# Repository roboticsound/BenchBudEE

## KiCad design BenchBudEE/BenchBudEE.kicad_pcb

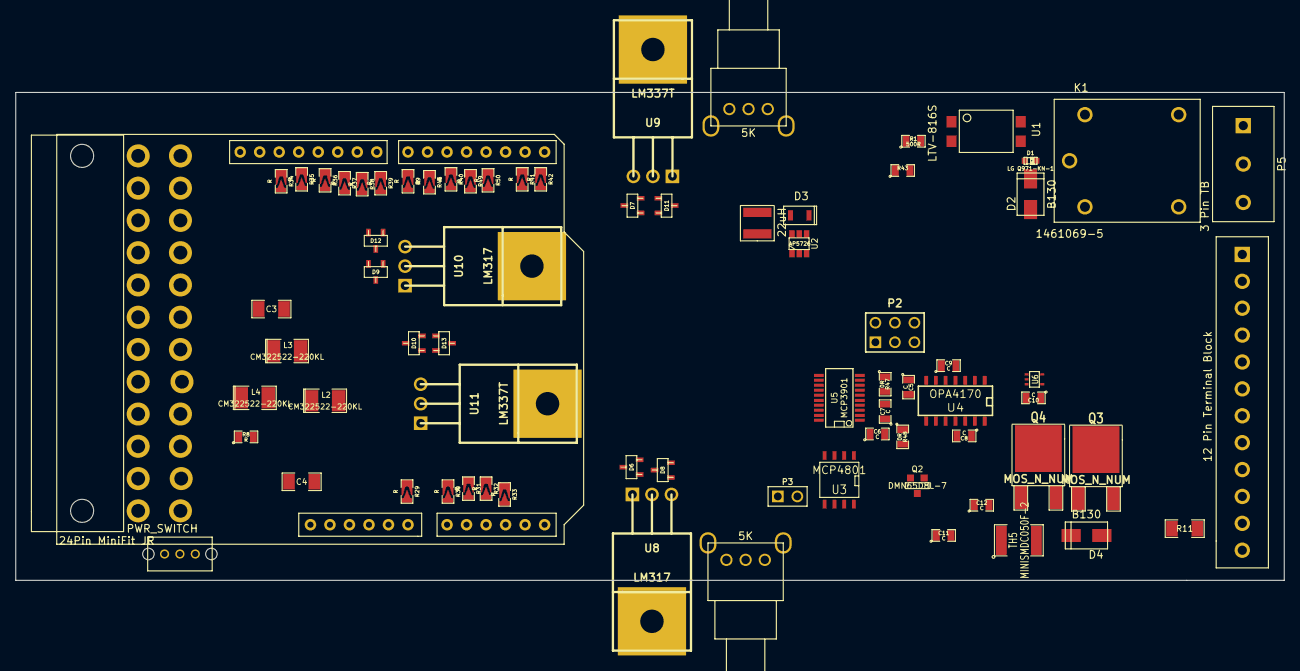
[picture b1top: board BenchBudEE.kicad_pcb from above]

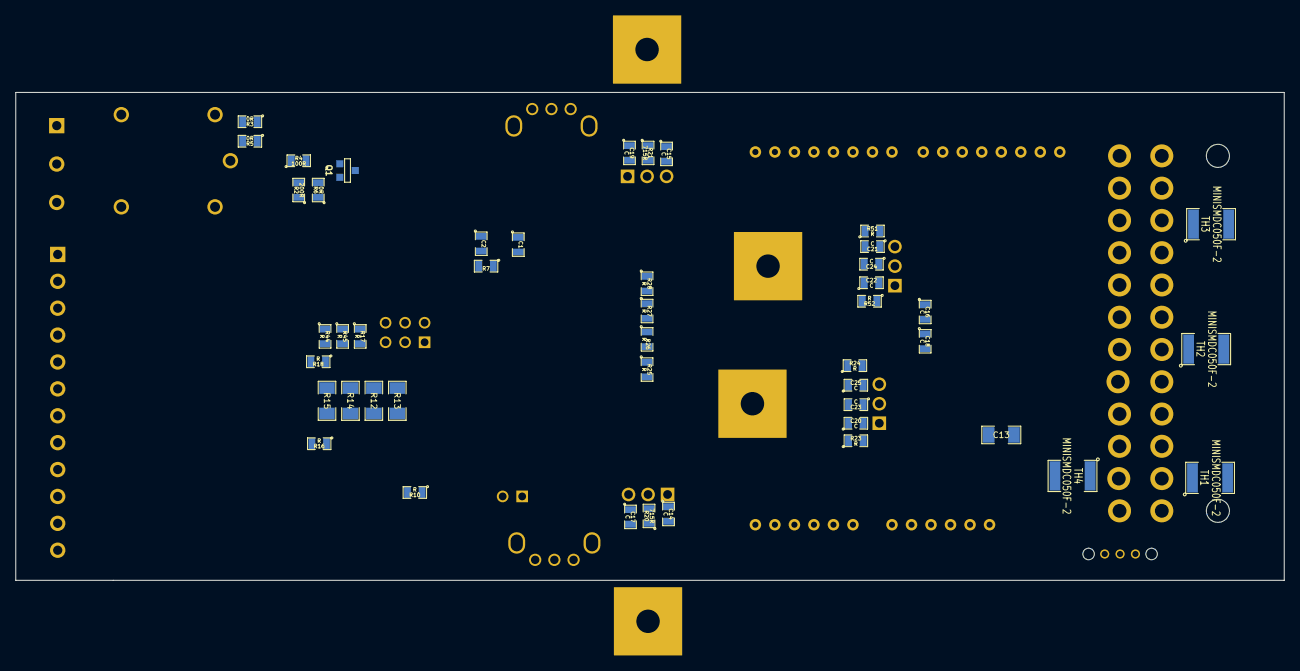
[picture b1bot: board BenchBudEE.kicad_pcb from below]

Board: 4 copper layers, 165.1 x 63.5 mm, 120 parts (46 on the bottom side), 96 nets, no tracks yet.

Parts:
ARD1: ARDUINOPINS; ARDUINO_UNO_HE
C1, C2: 1uF; SM0805
C3, C4, C13: C; SM1206
C5, C6, C7, C8, C9, C10, C11, C12, C14, C15, C16, C17, C18, C19, C20, C21, C22, C23, C24, C25: C; SM0805
D1: LG Q971-KN-1; LED-0603
D2, D4: B130; SMA
D3: B0540WS-7; SOD323
D6, D7, D8, D9, D10, D11, D12, D13: MMBD914-7-F; sot23
K1: 1461069-5; TE-SPDT
L1: 22uH; NR4012
L2, L3, L4: CM322522-220KL; SM1210L
P1: 24Pin MiniFit JR; ATX_24Header
P2: CONN_3X2; pin_array_3x2
P3: CONN_2; PIN_ARRAY_2X1
P4: 12 Pin Terminal Block; 12_PIN_TB
P5: 3 Pin TB; 3_PIN_TB
Q1: 2N3904; SOT23EBC
Q2: DMN65D8L-7; SOT23GDS
Q3, Q4: MOS_N_NUM; DPAK2
R1: 500R; SM0805
R2: 200R; SM0805
R3, R5, R6, R47, R48: 0R; SM0805
R4: 100R; SM0805
R7: 15R; SM0805
R8, R10, R16, R17, R18, R23, R24, R25, R26, R27, R28, R43, R44, R45, R51, R52: R; SM0805
R9, R29, R30, R31, R32, R33, R34, R35, R36, R37, R38, R39, R40, R41, R42, R46, R49, R50: R; SM0805_SolderBridge
R11, R12, R13, R14, R15: R; SM1206
R19, R22: 5K; POT_5K
R20, R21: 715R; SM0805
SW1: PWR_SWITCH
TH1, TH2, TH3, TH4, TH5: MINISMDC050F-2; SM1812
U1: LTV-816S; 4-SMD
U2: AP5726; SOT23_6
U3: MCP4801; SO8N
U4: OPA4170; SO14E
U5: MCP3901; SSOP20
U6: LMT84; SOT353
U8, U10: LM317; TO220
U9, U11: LM337T; TO220

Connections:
+3.3V: P4.1, R8.2, TH1.2
+5P: L4.1, TH2.2
+5V: C1.1, C7.1, C10.1, C13.1, L1.1, L4.2, P4.2, U2.6, U5.3, U6.4
+12C: C12.1, P1.10, TH3.1, TH5.1
+12P: L3.1, R3.2, R5.2, R29.1, TH3.2
+12V: C3.1, C9.2, C14.1, C16.1, D6.2, D9.2, L3.2, U4.4, U8.1, U10.1
-12P: L2.1, TH4.2
-12V: C4.2, C8.2, C15.2, C18.2, D7.2, D10.2, L2.2, U4.11, U9.2, U11.2
/Arduino/CURRENT_MEASURE: Q3.2, Q4.3, R11.1, R32.1, U4.9
/Arduino/FAN_MODE: Q3.1, R42.2
/Arduino/FAN_PWM: Q2.G, R37.2
/Arduino/LED_EN_PWM: R38.2, U2.4
/Arduino/MISO: R36.2, U5.19
/Arduino/MOSI: R35.2, U3.4, U5.20
/Arduino/RELAY+: R41.2, U1.1
/Arduino/RELAY-: R1.1, R43.2
/Arduino/SCLK: R34.2, U3.3, U5.18
/Arduino/~ADC_CS: R39.2, U5.17
/Arduino/~DR: R40.2, U5.14
/Arduino/~LDAC: R49.2, U3.5
/Arduino/~RESET: R46.2, U5.1
/Arduino/~SHDN: R50.2, U3.6
/FanDriver/FAN_OUT+: D4.2, P4.10, TH5.2
/FanDriver/TACH_IN: P4.8, R33.1
/FanDriver/~CS: R9.2, U3.2
/LED_Driver/LED_STRING+: C2.1, D3.2, P4.6, U2.5
/LED_Driver/LED_STRING-: P4.7, R7.1, U2.3
/Power/ATX_+3V3: P1.2, TH1.1
/Power/ATX_+5V: P1.4, P1.6, TH2.1
/Power/ATX_-12V: P1.14, TH4.1
/PowerAdjustmentMonitor/V+_ADJ: C22.1, D6.1, D8.2, P4.4, R20.2, R25.2, U8.3
/PowerAdjustmentMonitor/V+_ADJ_MON: R25.1, R26.2
/PowerAdjustmentMonitor/V-_ADJ: C23.2, D7.1, D11.1, P4.5, R21.2, R28.1, U9.3
/PowerAdjustmentMonitor/V-_ADJ_MON: R27.1, R28.2
/Relay/RELAY_COM: K1.1, P5.2
/Relay/RELAY_NC: K1.4, P5.3
/Relay/RELAY_NO: K1.3, P5.1
/TerminalBlock/FAN_OUT+: D4.1, P4.9, Q4.2
/Thermocouple/CH0+: C5.1, R12.2, U4.7, U5.4
/Thermocouple/CH0-: C5.2, R13.2, R48.1, U5.5
/Thermocouple/CH1-: R47.2, U5.6
/Thermocouple/Ch1+: U5.7, U6.3
/Thermocouple/TC IN+: P4.11, U4.12
/Thermocouple/TC IN-: P4.12, U4.3
AGND: C6.1, C7.2, C8.1, C9.1, C10.2, C11.1, C12.2, C14.2, C15.1, C16.2, C17.2, C18.1, C19.1, C20.1, C21.2, C24.2, C25.1, Q2.S, Q3.3, R11.2, R19.2, R22.1, R23.1, R26.1, R27.2, R47.1, R48.2, R52.2, U5.8, U5.11, U6.1, U6.2, U6.5
FE_V-: C22.2, C23.1, C24.1, C25.2, D9.1, D10.1, D12.2, D13.1, R24.2, R51.1, U10.3, U11.3
GND: C1.2, C2.2, C3.2, C4.1, C13.2, P1.3, P1.5, P4.3, R2.1, R6.1, R7.2, R43.1, SW1.3, U2.2
unnamed: P2.2, R45.1
unnamed: R17.2, R18.1, R44.2, R45.2, U4.2
unnamed: P2.4, R44.1
unnamed: P3.2, U5.13
unnamed: P3.1, U5.12
unnamed: R12.1, R14.2, U4.6
unnamed: R14.1, R16.2, U4.14
unnamed: R13.1, R15.2, U4.5
unnamed: R15.1, R18.2, U4.1
unnamed: P2.6, R17.1
unnamed: C6.2, U5.2
unnamed: P2.1, P2.3, P2.5, R16.1, U4.13
unnamed: C11.2, U3.1
unnamed: Q4.1, U4.8
unnamed: Q2.D, R10.2, U4.10
unnamed: R10.1, U3.8
unnamed: ARD1.7, R30.2
unnamed: ARD1.23, R37.1
unnamed: ARD1.8, R31.2
unnamed: ARD1.24, R36.1
unnamed: ARD1.25, R35.1
unnamed: ARD1.26, R34.1
unnamed: ARD1.9, R32.2
unnamed: ARD1.10, R33.2
unnamed: ARD1.14, R41.1
unnamed: ARD1.16, R50.1
unnamed: ARD1.6, R29.2
unnamed: ARD1.13, R42.1
unnamed: ARD1.18, R40.1
unnamed: ARD1.21, R39.1
unnamed: ARD1.22, R38.1
unnamed: ARD1.19, R46.1
unnamed: ARD1.17, R49.1
unnamed: ARD1.20, R9.1
unnamed: R1.2, U1.2
unnamed: R3.1, U1.4
unnamed: D2.1, K1.5, Q1.3
unnamed: D1.1, R4.1, U1.3
unnamed: Q1.2, R4.2
unnamed: Q1.1, R6.2
unnamed: D2.2, K1.2, R5.1
unnamed: D1.2, R2.2
unnamed: D3.1, L1.2, U2.1
unnamed: P1.16, SW1.2
unnamed: R8.1, SW1.1
unnamed: C21.1, D12.1, R51.2, R52.1, U10.2
unnamed: C19.2, D11.2, R21.1, R22.2, U9.1
unnamed: C20.2, D13.2, R23.2, R24.1, U11.1
unnamed: C17.1, D8.1, R19.1, R20.1, U8.2

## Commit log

2014-01-30 Schematic/PCB blank files created
2014-02-04 Intial block diagram, added new .sch sheets for each module
2014-02-04 Added initial module I/O
2014-02-05 Created thermocouple module block diagram
2014-02-05 Created Fan Module block diagram + added new I/O + minor spelling corrections
2014-02-05 Created Relay block diagram
2014-02-05 Power module blocked out + added power adjustment monitor module
2014-02-06 Power monitor module blocked out (needs tidying)
2014-02-06 LED Driver module sketched out from AP5726 chip
2014-02-08 Schematic modules connected together and to arduino pins
2014-02-19 Parts added to relay module. Schematic tidied up.
2014-02-20 Design rules specified for layout.
2014-02-21 Parts added to thermocouple module. Relay & thermocouple rough placement.
2014-02-21 Connectors added + associated + roughly placed.
2014-02-23 Arduino module associated + roughly placed.
2014-02-23 Modified 0805 SB footprint.
2014-02-23 Fan/Current driver associated + roughly placed.
2014-02-23 Power Module associated + roughly placed.
2014-02-25 All modules (inc. LED Driver) associated + roughly placed.
